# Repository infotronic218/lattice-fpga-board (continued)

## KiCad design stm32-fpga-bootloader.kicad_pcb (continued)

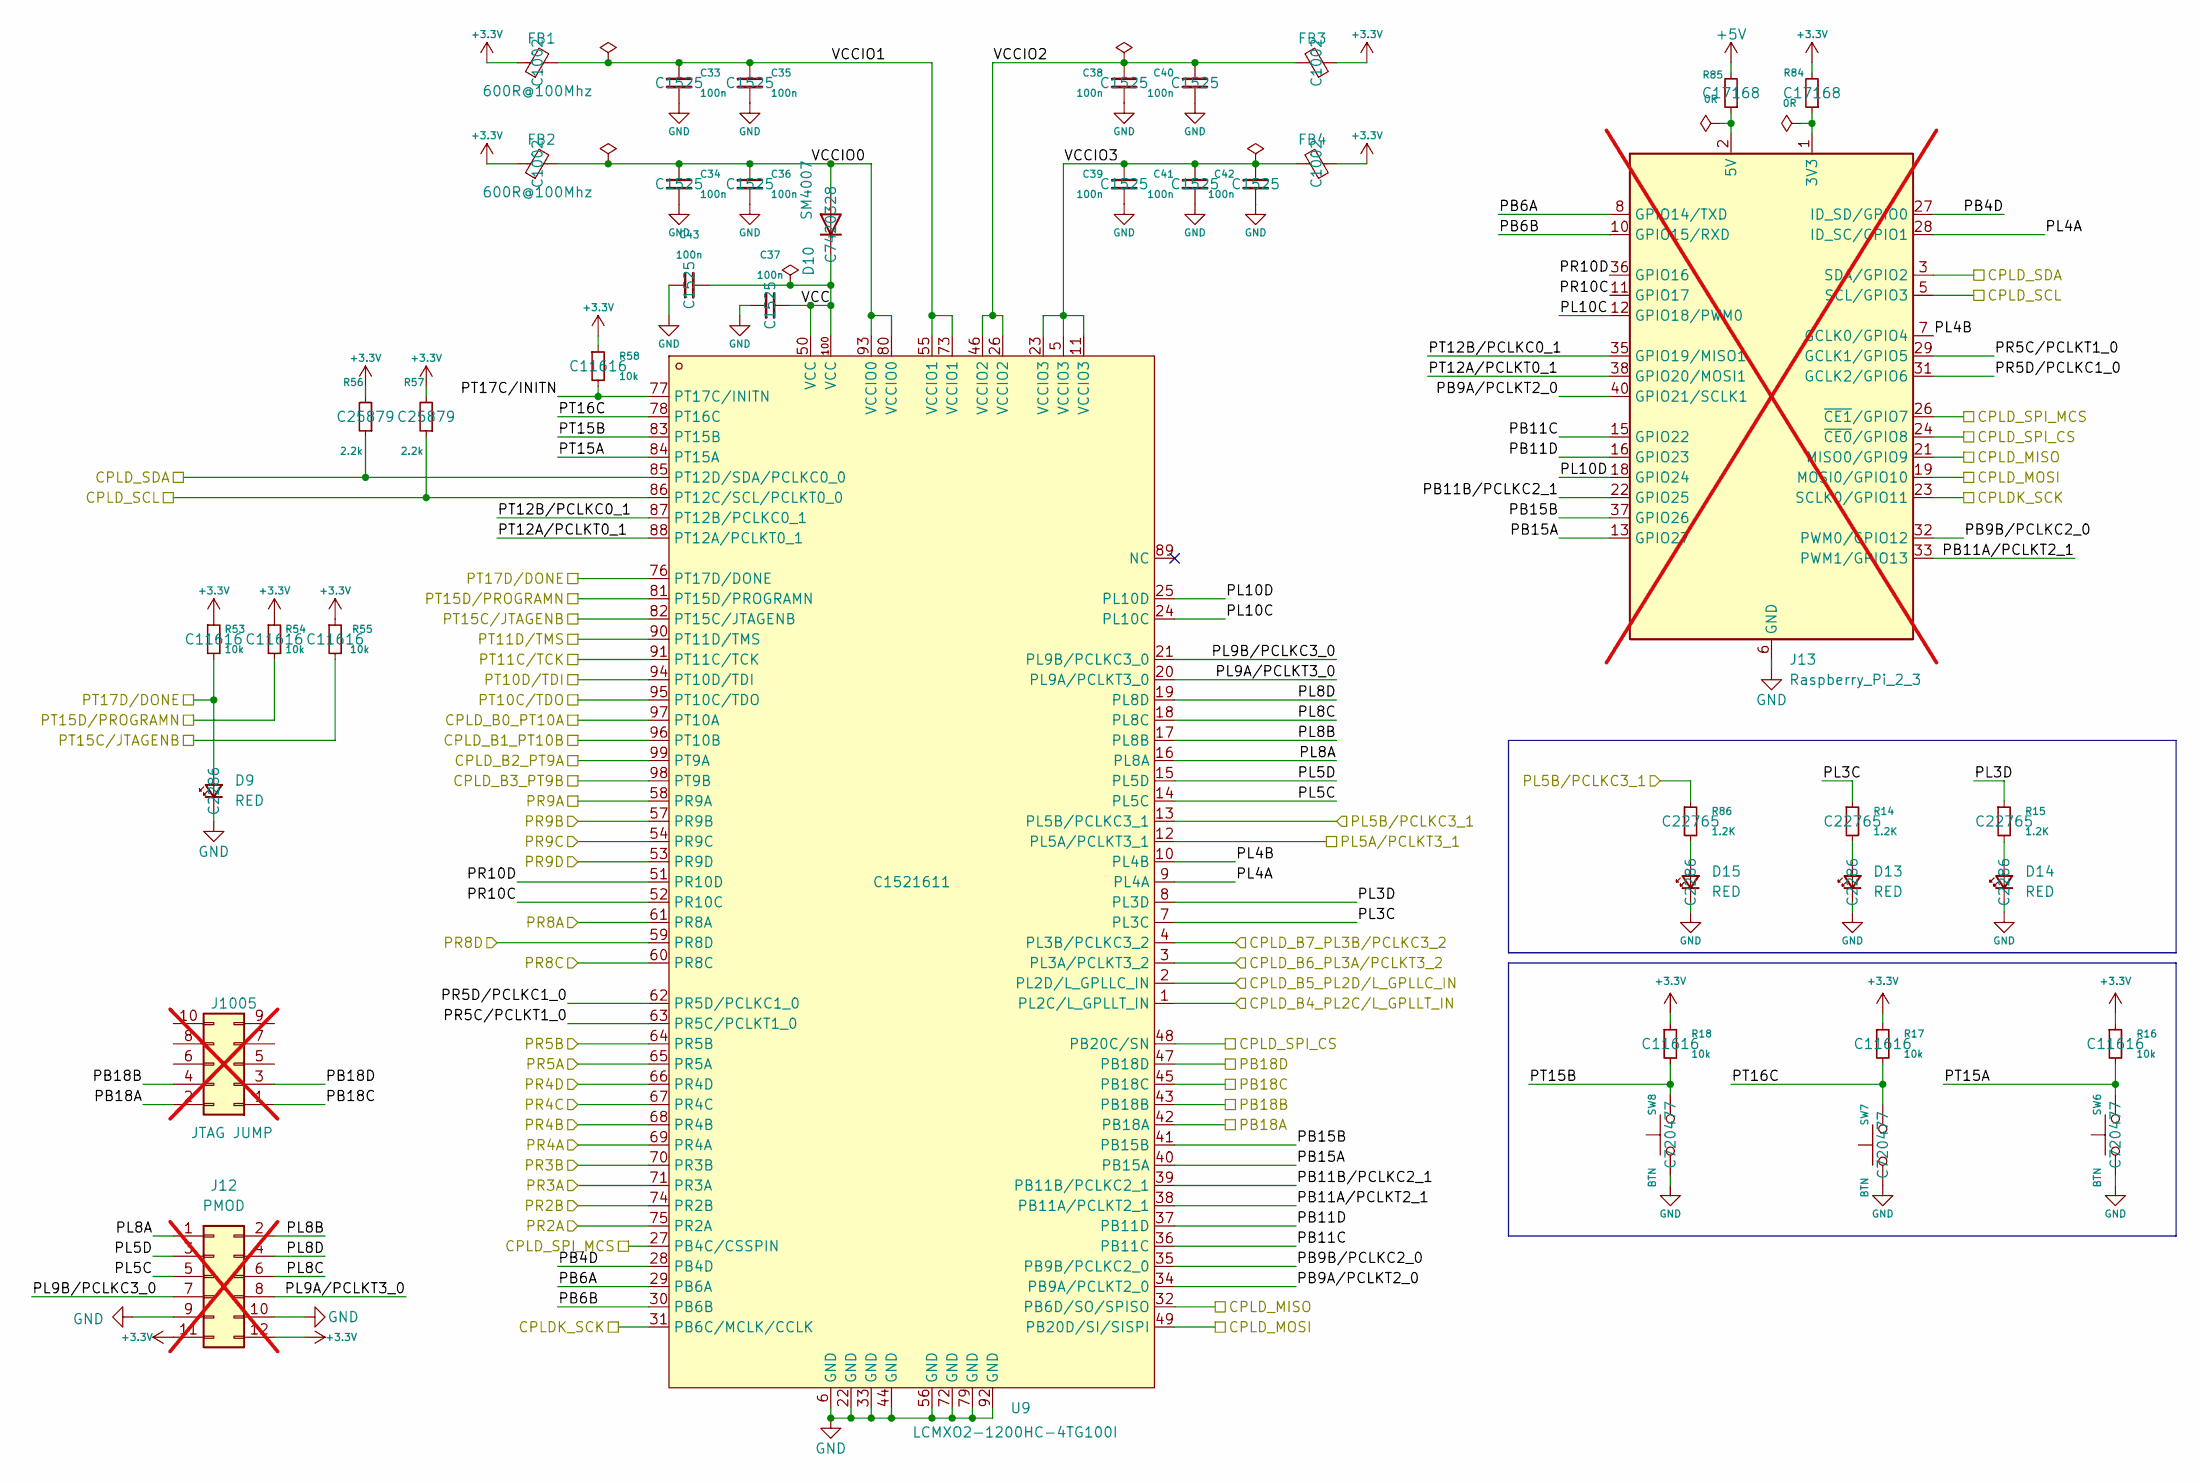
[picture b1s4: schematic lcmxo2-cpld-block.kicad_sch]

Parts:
C33, C34, C35, C36, C37, C38, C39, C40, C41, C42, C43: 100n; C_0402_1005Metric; LCSC C1525
D9, D13, D14, D15: RED; LED_0603_1608Metric; LCSC C2286
D10: SM4007; D_SOD-123F; LCSC C7420328
FB1, FB2, FB3, FB4: 600R@100Mhz; L_0603_1608Metric; LCSC C1002
J12: PMOD; PinSocket_2x06_P2.54mm_Horizontal; not fitted
J13: Raspberry_Pi_2_3; PinHeader_2x20_P2.54mm_Vertical; not fitted
J1005: JTAG JUMP; PinSocket_2x05_P2.54mm_Vertical; not fitted
R14, R15, R86: 1.2K; R_0603_1608Metric; LCSC C22765
R16, R17, R18, R53, R54, R55, R58: 10k; R_0402_1005Metric; LCSC C11616
R56, R57: 2.2k; R_0402_1005Metric; LCSC C25879
R84, R85: 0R; R_0402_1005Metric; LCSC C17168
SW6, SW7, SW8: BTN; SW-SMD_L3.9-W3.0-P4.45; LCSC C720477
U9: LCMXO2-1200HC-4TG100I; TQFP-100_14x14mm_P0.5mm; LCSC Part Name LCMXO2 1200HC 4TG100I

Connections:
+3.3V: FB1.1, FB2.1, FB3.1, FB4.1, J12.11, J12.12, R16.1, R17.1, R18.1, R53.1, R54.1, R55.1, R56.2, R57.2, R58.1, R84.2; also elsewhere on the board
+5V: R85.2; also elsewhere on the board
/CPLDK_SCK: J13.23 (SCLK0/GPIO11), U9.31 (PB6C/MCLK/CCLK); also elsewhere on the board
/CPLD_B0_PT10A: U9.97 (PT10A); also elsewhere on the board
/CPLD_B1_PT10B: U9.96 (PT10B); also elsewhere on the board
/CPLD_B2_PT9A: U9.99 (PT9A); also elsewhere on the board
/CPLD_B3_PT9B: U9.98 (PT9B); also elsewhere on the board
/CPLD_B4_PL2C/L_GPLLT_IN: U9.1 (PL2C/L_GPLLT_IN); also elsewhere on the board
/CPLD_B5_PL2D/L_GPLLC_IN: U9.2 (PL2D/L_GPLLC_IN); also elsewhere on the board
/CPLD_B6_PL3A/PCLKT3_2: U9.3 (PL3A/PCLKT3_2); also elsewhere on the board
/CPLD_B7_PL3B/PCLKC3_2: U9.4 (PL3B/PCLKC3_2); also elsewhere on the board
/CPLD_CLOCK: U9.12 (PL5A/PCLKT3_1); also elsewhere on the board
/CPLD_MISO: J13.21 (MISO0/GPIO9), U9.32 (PB6D/SO/SPISO); also elsewhere on the board
/CPLD_MOSI: J13.19 (MOSI0/GPIO10), U9.49 (PB20D/SI/SISPI); also elsewhere on the board
/CPLD_SCL: J13.5 (SCL/GPIO3), R57.1, U9.86 (PT12C/SCL/PCLKT0_0); also elsewhere on the board
/CPLD_SDA: J13.3 (SDA/GPIO2), R56.1, U9.85 (PT12D/SDA/PCLKC0_0); also elsewhere on the board
/CPLD_SPI_CS: J13.24 (~CE0/GPIO8), U9.48 (PB20C/SN); also elsewhere on the board
/CPLD_SPI_MCS: J13.26 (~CE1/GPIO7), U9.27 (PB4C/CSSPIN); also elsewhere on the board
/PB18A: J1005.2, U9.42 (PB18A)
/PB18B: J1005.4, U9.43 (PB18B)
/PB18C: J1005.1, U9.45 (PB18C)
/PB18D: J1005.3, U9.47 (PB18D)
/PR2A: U9.75 (PR2A); also elsewhere on the board
/PR2B: U9.74 (PR2B); also elsewhere on the board
/PR3A: U9.71 (PR3A); also elsewhere on the board
/PR3B: U9.70 (PR3B); also elsewhere on the board
/PR4A: U9.69 (PR4A); also elsewhere on the board
/PR4B: U9.68 (PR4B); also elsewhere on the board
/PR4C: U9.67 (PR4C); also elsewhere on the board
/PR4D: U9.66 (PR4D); also elsewhere on the board
/PR5A: U9.65 (PR5A); also elsewhere on the board
/PR5B: U9.64 (PR5B); also elsewhere on the board
/PR8A: U9.61 (PR8A); also elsewhere on the board
/PR8C: U9.60 (PR8C); also elsewhere on the board
/PR8D: U9.59 (PR8D); also elsewhere on the board
/PR9A: U9.58 (PR9A); also elsewhere on the board
/PR9B: U9.57 (PR9B); also elsewhere on the board
/PR9C: U9.54 (PR9C); also elsewhere on the board
/PR9D: U9.53 (PR9D); also elsewhere on the board
/PT10C/TDO: U9.95 (PT10C/TDO); also elsewhere on the board
/PT10D/TDI: U9.94 (PT10D/TDI); also elsewhere on the board
/PT11C/TCK: U9.91 (PT11C/TCK); also elsewhere on the board
/PT11D/TMS: U9.90 (PT11D/TMS); also elsewhere on the board
/jtag-prog/CLK: R86.1, U9.13 (PL5B/PCLKC3_1); also elsewhere on the board
/lcmxo2-cpld-block/PB4D: J13.27 (ID_SD/GPIO0), U9.28 (PB4D)
/lcmxo2-cpld-block/PB6A: J13.8 (GPIO14/TXD), U9.29 (PB6A)
/lcmxo2-cpld-block/PB6B: J13.10 (GPIO15/RXD), U9.30 (PB6B)
/lcmxo2-cpld-block/PB9A/PCLKT2_0: J13.40 (GPIO21/SCLK1), U9.34 (PB9A/PCLKT2_0)
/lcmxo2-cpld-block/PB9B/PCLKC2_0: J13.32 (PWM0/GPIO12), U9.35 (PB9B/PCLKC2_0)
/lcmxo2-cpld-block/PB11A/PCLKT2_1: J13.33 (PWM1/GPIO13), U9.38 (PB11A/PCLKT2_1)
/lcmxo2-cpld-block/PB11B/PCLKC2_1: J13.22 (GPIO25), U9.39 (PB11B/PCLKC2_1)
/lcmxo2-cpld-block/PB11C: J13.15 (GPIO22), U9.36 (PB11C)
/lcmxo2-cpld-block/PB11D: J13.16 (GPIO23), U9.37 (PB11D)
/lcmxo2-cpld-block/PB15A: J13.13 (GPIO27), U9.40 (PB15A)
/lcmxo2-cpld-block/PB15B: J13.37 (GPIO26), U9.41 (PB15B)
/lcmxo2-cpld-block/PL3C: R14.1, U9.7 (PL3C)
/lcmxo2-cpld-block/PL3D: R15.1, U9.8 (PL3D)
/lcmxo2-cpld-block/PL4A: J13.28 (ID_SC/GPIO1), U9.9 (PL4A)
/lcmxo2-cpld-block/PL4B: J13.7 (GCLK0/GPIO4), U9.10 (PL4B)
/lcmxo2-cpld-block/PL5C: J12.5, U9.14 (PL5C)
/lcmxo2-cpld-block/PL5D: J12.3, U9.15 (PL5D)
/lcmxo2-cpld-block/PL8A: J12.1, U9.16 (PL8A)
/lcmxo2-cpld-block/PL8B: J12.2, U9.17 (PL8B)
/lcmxo2-cpld-block/PL8C: J12.6, U9.18 (PL8C)
/lcmxo2-cpld-block/PL8D: J12.4, U9.19 (PL8D)
/lcmxo2-cpld-block/PL9A/PCLKT3_0: J12.8, U9.20 (PL9A/PCLKT3_0)
/lcmxo2-cpld-block/PL9B/PCLKC3_0: J12.7, U9.21 (PL9B/PCLKC3_0)
/lcmxo2-cpld-block/PL10C: J13.12 (GPIO18/PWM0), U9.24 (PL10C)
/lcmxo2-cpld-block/PL10D: J13.18 (GPIO24), U9.25 (PL10D)
/lcmxo2-cpld-block/PR5C/PCLKT1_0: J13.29 (GCLK1/GPIO5), U9.63 (PR5C/PCLKT1_0)
/lcmxo2-cpld-block/PR5D/PCLKC1_0: J13.31 (GCLK2/GPIO6), U9.62 (PR5D/PCLKC1_0)
/lcmxo2-cpld-block/PR10C: J13.11 (GPIO17), U9.52 (PR10C)
/lcmxo2-cpld-block/PR10D: J13.36 (GPIO16), U9.51 (PR10D)
/lcmxo2-cpld-block/PT12A/PCLKT0_1: J13.38 (GPIO20/MOSI1), U9.88 (PT12A/PCLKT0_1)
/lcmxo2-cpld-block/PT12B/PCLKC0_1: J13.35 (GPIO19/MISO1), U9.87 (PT12B/PCLKC0_1)
/lcmxo2-cpld-block/PT15A: R16.2, SW6.2, U9.84 (PT15A)
/lcmxo2-cpld-block/PT15B: R18.2, SW8.2, U9.83 (PT15B)
/lcmxo2-cpld-block/PT15C/JTAGENB: R55.2, U9.82 (PT15C/JTAGENB)
/lcmxo2-cpld-block/PT15D/PROGRAMN: R54.2, U9.81 (PT15D/PROGRAMN)
/lcmxo2-cpld-block/PT16C: R17.2, SW7.2, U9.78 (PT16C)
/lcmxo2-cpld-block/PT17C/INITN: R58.2, U9.77 (PT17C/INITN)
/lcmxo2-cpld-block/PT17D/DONE: D9.2 (A), R53.2, U9.76 (PT17D/DONE)
/lcmxo2-cpld-block/VCC: C37.2, C43.2, D10.1 (K), U9.50 (VCC), U9.100 (VCC)
/lcmxo2-cpld-block/VCCIO0: C34.1, C36.1, D10.2 (A), FB2.2, U9.80 (VCCIO0), U9.93 (VCCIO0)
/lcmxo2-cpld-block/VCCIO1: C33.1, C35.1, FB1.2, U9.55 (VCCIO1), U9.73 (VCCIO1)
/lcmxo2-cpld-block/VCCIO2: C38.1, C40.1, FB3.2, U9.26 (VCCIO2), U9.46 (VCCIO2)
/lcmxo2-cpld-block/VCCIO3: C39.1, C41.1, C42.1, FB4.2, U9.5 (VCCIO3), U9.11 (VCCIO3), U9.23 (VCCIO3)
GND: C33.2, C34.2, C35.2, C36.2, C37.1, C38.2, C39.2, C40.2, C41.2, C42.2, C43.1, D9.1 (K), D13.1 (K), D14.1 (K), D15.1 (K), J12.9, J12.10, J13.6 (GND), J13.9 (GND), J13.14 (GND), J13.20 (GND), J13.25 (GND), J13.30 (GND), J13.34 (GND), J13.39 (GND), SW6.1, SW7.1, SW8.1, U9.6 (GND), U9.22 (GND), U9.33 (GND), U9.44 (GND), U9.56 (GND), U9.72 (GND), U9.79 (GND), U9.92 (GND); also elsewhere on the board
unnamed: D13.2 (A), R14.2
unnamed: D14.2 (A), R15.2
unnamed: D15.2 (A), R86.2
unnamed: J13.1 (3V3), J13.17 (3V3), R84.1
unnamed: J13.2 (5V), J13.4 (5V), R85.1

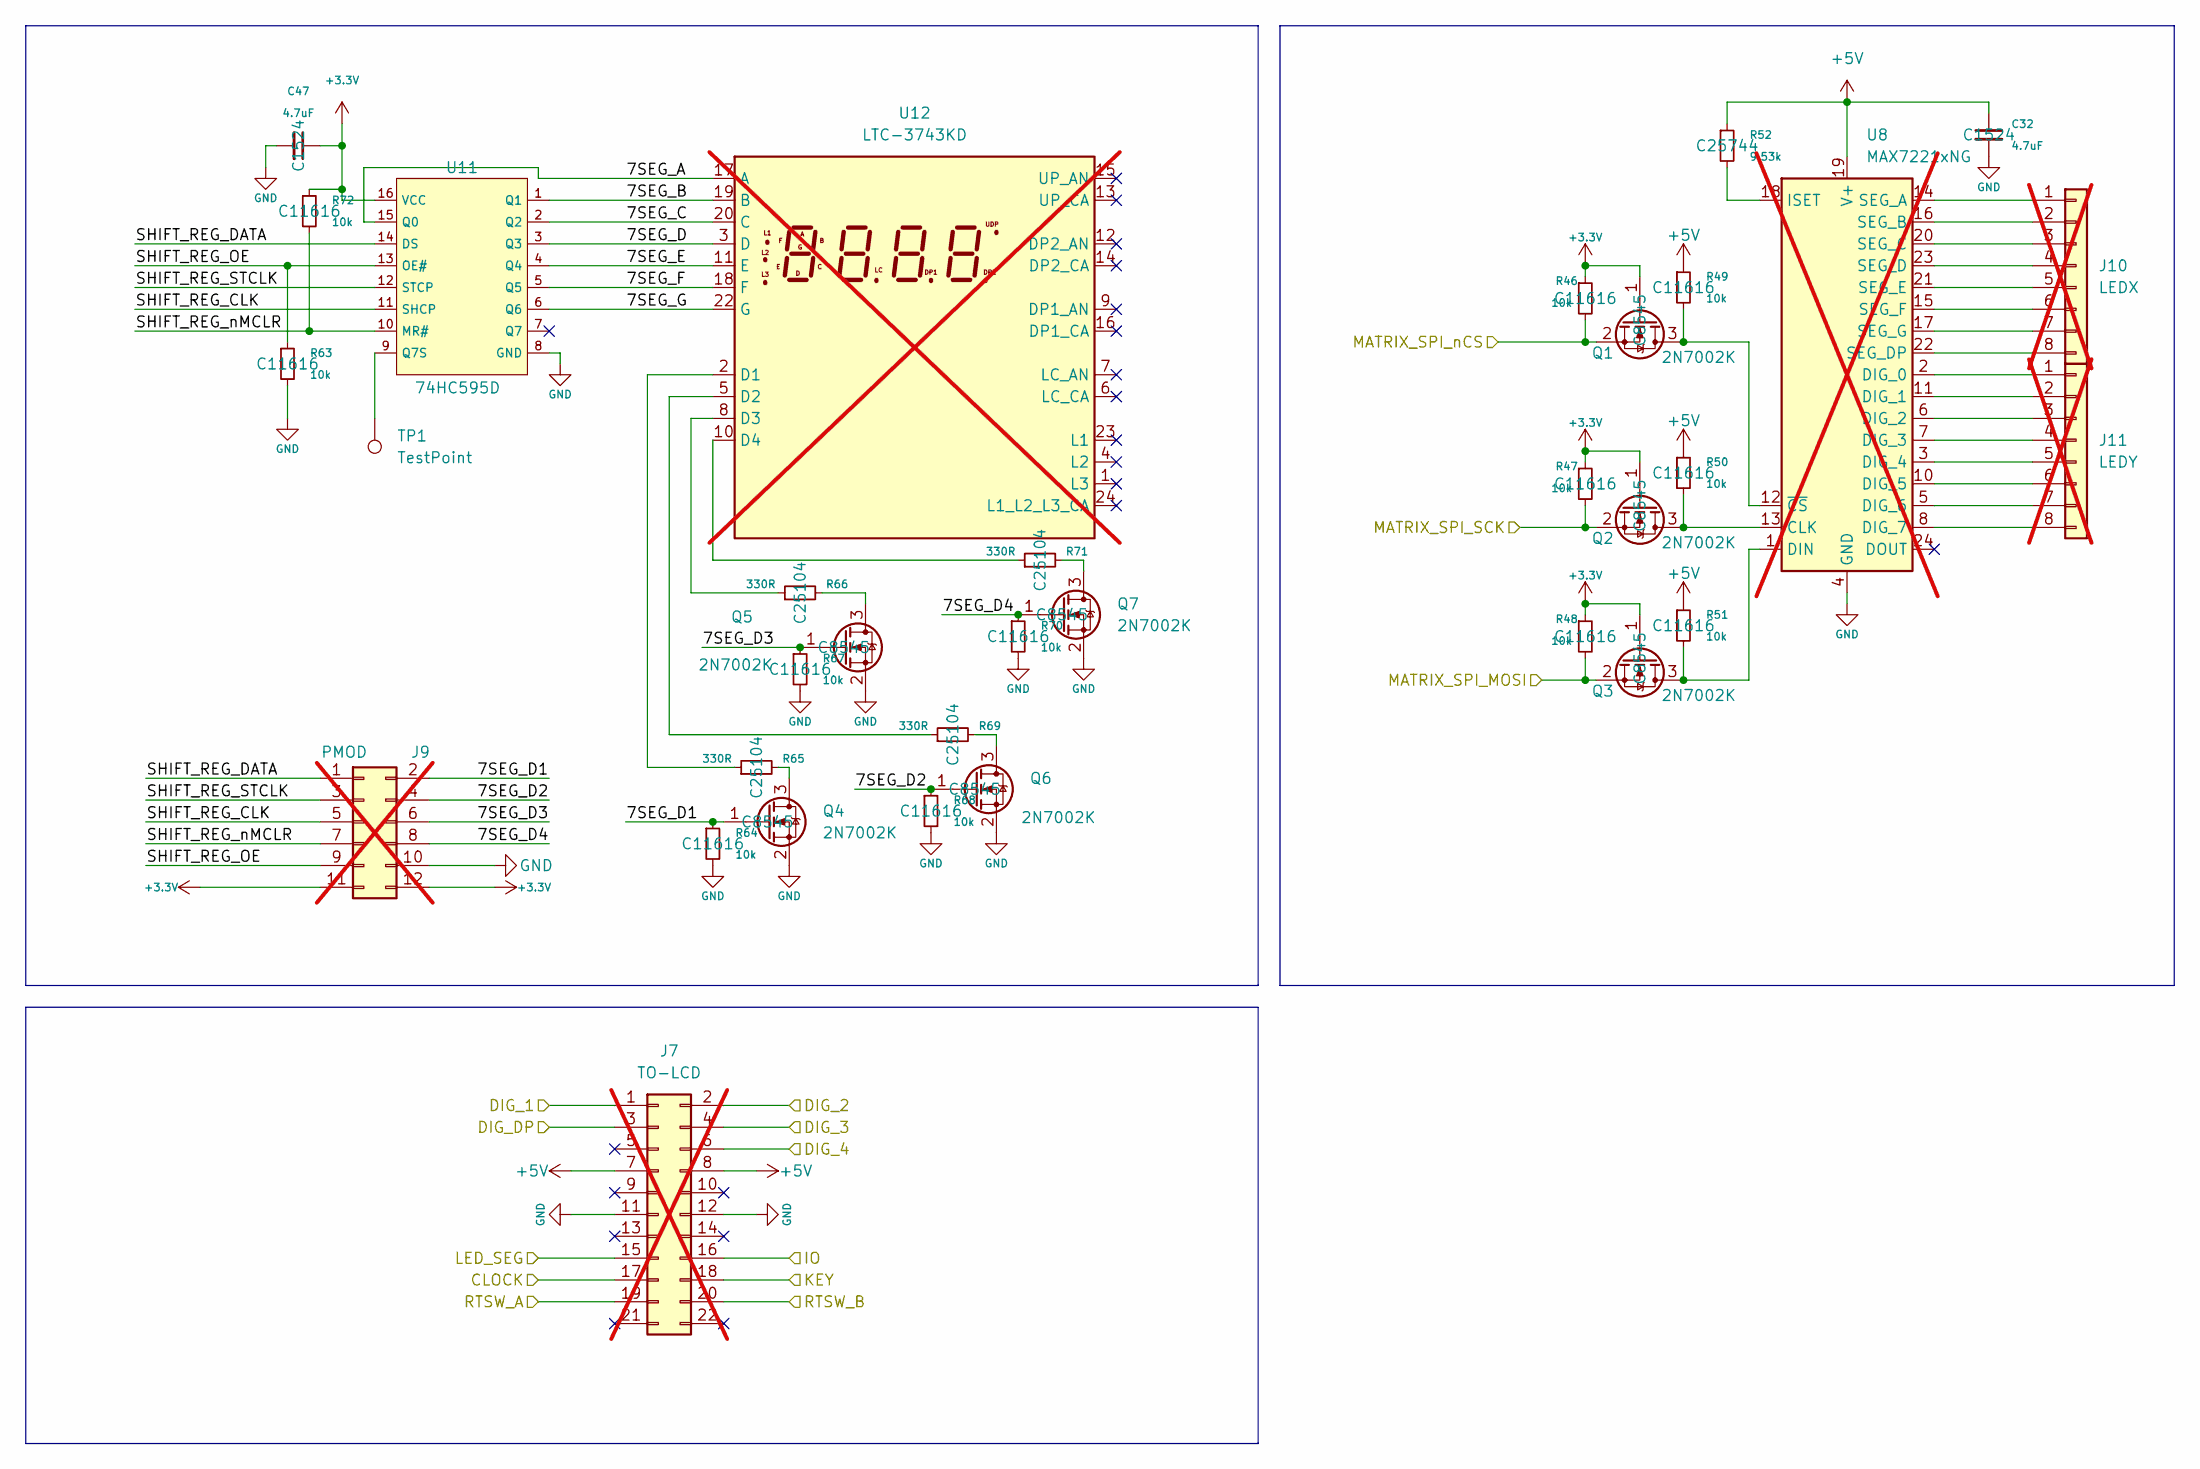
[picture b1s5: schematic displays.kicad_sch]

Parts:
C32, C47: 4.7uF; C_0603_1608Metric; LCSC C1524
J7: TO-LCD; CON_536470274_MOL; not fitted
J9: PMOD; PinSocket_2x06_P2.54mm_Vertical; not fitted
J10: LEDX; PinSocket_1x08_P2.54mm_Vertical; not fitted
J11: LEDY; PinSocket_1x08_P2.54mm_Vertical; not fitted
Q1, Q2, Q3, Q4, Q5, Q6, Q7: 2N7002K; SOT-23; LCSC C8545
R46, R47, R48, R49, R50, R51, R63, R64, R67, R68, R70, R72: 10k; R_0402_1005Metric; LCSC C11616
R52: 9.53k; R_0402_1005Metric; LCSC C25744
R65, R66, R69, R71: 330R; R_0402_1005Metric; LCSC C25104
TP1: TestPoint; TestPoint_Pad_1.0x1.0mm
U8: MAX7221xNG; DIP-24_W7.62mm; not fitted
U11: 74HC595D; SOIC-16_L9.9-W3.9-P1.27-LS6.0-BL; LCSC C5947
U12: LTC-3743KD; not fitted

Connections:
+3.3V: C47.1, J9.11, J9.12, Q1.1 (G), Q2.1 (G), Q3.1 (G), R46.1, R47.1, R48.1, R72.1, U11.16 (VCC); also elsewhere on the board
+5V: C32.1, J7.7, J7.8, R49.1, R50.1, R51.1, R52.1, U8.19 (V+); also elsewhere on the board
/MATRIX_SPI_MOSI: Q3.2 (S), R48.2; also elsewhere on the board
/MATRIX_SPI_SCK: Q2.2 (S), R47.2; also elsewhere on the board
/MATRIX_SPI_nCS: Q1.2 (S), R46.2; also elsewhere on the board
/PR4C: J7.1; also elsewhere on the board
/PR4D: J7.3; also elsewhere on the board
/PR5A: J7.2; also elsewhere on the board
/PR5B: J7.4; also elsewhere on the board
/PR8A: J7.6; also elsewhere on the board
/PR8C: J7.16; also elsewhere on the board
/PR8D: J7.18; also elsewhere on the board
/PR9A: J7.20; also elsewhere on the board
/PR9B: J7.17; also elsewhere on the board
/PR9C: J7.19; also elsewhere on the board
/PR9D: J7.15; also elsewhere on the board
/displays/7SEG_A: U11.15 (Q0), U12.17 (A)
/displays/7SEG_B: U11.1 (Q1), U12.19 (B)
/displays/7SEG_C: U11.2 (Q2), U12.20 (C)
/displays/7SEG_D: U11.3 (Q3), U12.3 (D)
/displays/7SEG_D1: J9.2, Q4.1 (G), R64.1
/displays/7SEG_D2: J9.4, Q6.1 (G), R68.1
/displays/7SEG_D3: J9.6, Q5.1 (G), R67.1
/displays/7SEG_D4: J9.8, Q7.1 (G), R70.1
/displays/7SEG_E: U11.4 (Q4), U12.11 (E), U12.21 (D1_E_AN)
/displays/7SEG_F: U11.5 (Q5), U12.18 (F)
/displays/7SEG_G: U11.6 (Q6), U12.22 (G)
/displays/SHIFT_REG_CLK: J9.5, U11.11 (SHCP)
/displays/SHIFT_REG_DATA: J9.1, U11.14 (DS)
/displays/SHIFT_REG_OE: J9.9, R63.1, U11.13 (OE#)
/displays/SHIFT_REG_STCLK: J9.3, U11.12 (STCP)
/displays/SHIFT_REG_nMCLR: J9.7, R72.2, U11.10 (MR#)
GND: C32.2, C47.2, J7.11, J7.12, J9.10, Q4.2 (S), Q5.2 (S), Q6.2 (S), Q7.2 (S), R63.2, R64.2, R67.2, R68.2, R70.2, U8.4 (GND), U8.9 (GND), U11.8 (GND); also elsewhere on the board
unnamed: J10.1, U8.14 (SEG_A)
unnamed: J10.2, U8.16 (SEG_B)
unnamed: J10.3, U8.20 (SEG_C)
unnamed: J10.4, U8.23 (SEG_D)
unnamed: J10.5, U8.21 (SEG_E)
unnamed: J10.6, U8.15 (SEG_F)
unnamed: J10.7, U8.17 (SEG_G)
unnamed: J10.8, U8.22 (SEG_DP)
unnamed: J11.1, U8.2 (DIG_0)
unnamed: J11.2, U8.11 (DIG_1)
unnamed: J11.3, U8.6 (DIG_2)
unnamed: J11.4, U8.7 (DIG_3)
unnamed: J11.5, U8.3 (DIG_4)
unnamed: J11.6, U8.10 (DIG_5)
unnamed: J11.7, U8.5 (DIG_6)
unnamed: J11.8, U8.8 (DIG_7)
unnamed: Q1.3 (D), R49.2, U8.12 (~CS)
unnamed: Q2.3 (D), R50.2, U8.13 (CLK)
unnamed: Q3.3 (D), R51.2, U8.1 (DIN)
unnamed: Q4.3 (D), R65.2
unnamed: Q5.3 (D), R66.2
unnamed: Q6.3 (D), R69.2
unnamed: Q7.3 (D), R71.2
unnamed: R52.2, U8.18 (ISET)
unnamed: TP1.1, U11.9 (Q7S)
unnamed: R65.1, U12.2 (D1)
unnamed: R69.1, U12.5 (D2)
unnamed: R66.1, U12.8 (D3)
unnamed: R71.1, U12.10 (D4)

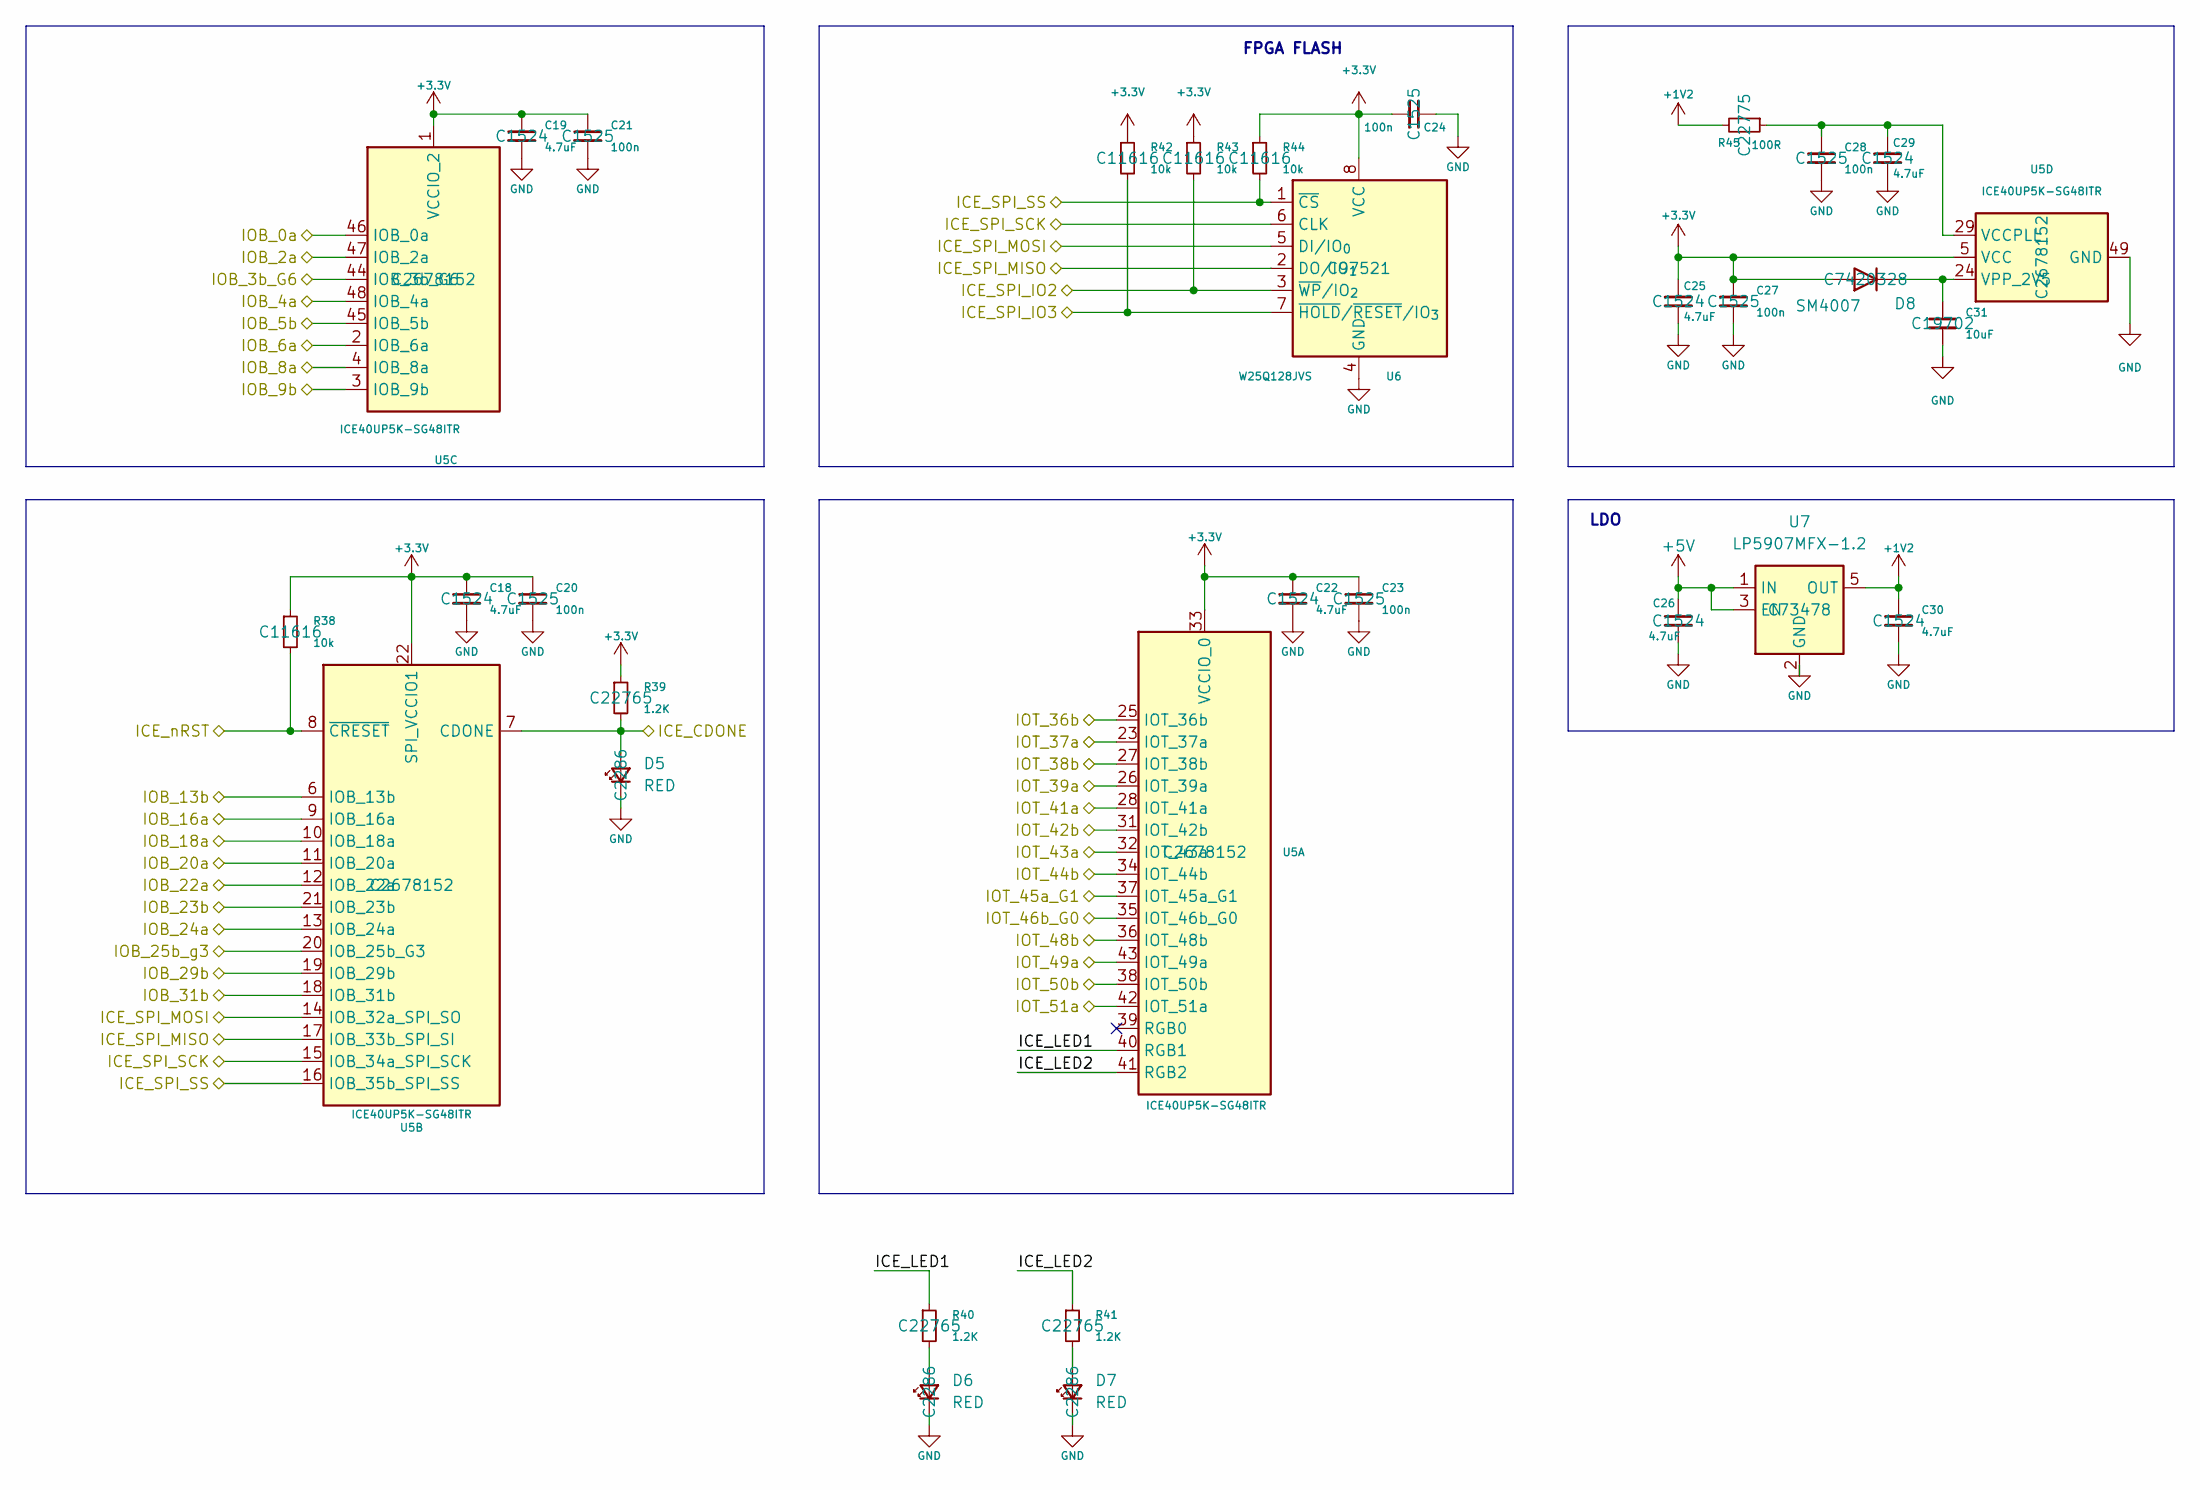
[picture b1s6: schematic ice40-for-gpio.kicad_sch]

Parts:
C18, C19, C22, C25, C26, C29, C30: 4.7uF; C_0603_1608Metric; LCSC C1524
C20, C21, C23, C24, C27, C28: 100n; C_0402_1005Metric; LCSC C1525
C31: 10uF; C_0603_1608Metric; LCSC C19702
D5, D6, D7: RED; LED_0603_1608Metric; LCSC C2286
D8: SM4007; D_SOD-123F; LCSC C7420328
R38, R42, R43, R44: 10k; R_0402_1005Metric; LCSC C11616
R39, R40, R41: 1.2K; R_0603_1608Metric; LCSC C22765
R45: 100R; R_0603_1608Metric; LCSC C22775
U5: ICE40UP5K-SG48ITR; QFN-48-1EP_7x7mm_P0.5mm_EP5.6x5.6mm; LCSC C2678152
U6: W25Q128JVS; SOIC-8_5.3x5.3mm_P1.27mm; LCSC C97521
U7: LP5907MFX-1.2; SOT-23-5; LCSC C73478

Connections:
+1V2: C30.1, R45.2, U7.5 (OUT)
+3.3V: C18.1, C19.1, C20.1, C21.1, C22.1, C23.1, C24.2, C25.1, C27.1, D8.2 (A), R38.1, R39.1, R42.1, R43.1, R44.1, U5.1 (VCCIO_2), U5.5 (VCC), U5.22 (SPI_VCCIO1), U5.30 (VCC), U5.33 (VCCIO_0), U6.8 (VCC); also elsewhere on the board
+5V: C26.1, U7.1 (IN), U7.3 (EN); also elsewhere on the board
/ICE_CDONE: D5.2 (A), R39.2, U5.7 (CDONE); also elsewhere on the board
/ICE_CLOCK: U5.35 (IOT_46b_G0); also elsewhere on the board
/ICE_SPI_MISO: U5.17 (IOB_33b_SPI_SI), U6.2 (DO/IO_{1}); also elsewhere on the board
/ICE_SPI_MOSI: U5.14 (IOB_32a_SPI_SO), U6.5 (DI/IO_{0}); also elsewhere on the board
/ICE_SPI_SCK: U5.15 (IOB_34a_SPI_SCK), U6.6 (CLK); also elsewhere on the board
/ICE_SPI_SS: R44.2, U5.16 (IOB_35b_SPI_SS), U6.1 (~CS); also elsewhere on the board
/ICE_USB_N: U5.9 (IOB_16a); also elsewhere on the board
/ICE_USB_P: U5.10 (IOB_18a); also elsewhere on the board
/ICE_nRST: R38.2, U5.8 (~CRESET); also elsewhere on the board
/IOB_0a: U5.46 (IOB_0a); also elsewhere on the board
/IOB_2a: U5.47 (IOB_2a); also elsewhere on the board
/IOB_3b_G6: U5.44 (IOB_3b_G6); also elsewhere on the board
/IOB_4a: U5.48 (IOB_4a); also elsewhere on the board
/IOB_5b: U5.45 (IOB_5b); also elsewhere on the board
/IOB_6a: U5.2 (IOB_6a); also elsewhere on the board
/IOB_8a: U5.4 (IOB_8a); also elsewhere on the board
/IOB_13b: U5.6 (IOB_13b); also elsewhere on the board
/IOB_20a: U5.11 (IOB_20a); also elsewhere on the board
/IOB_22a: U5.12 (IOB_22a); also elsewhere on the board
/IOB_23b: U5.21 (IOB_23b); also elsewhere on the board
/IOT_36b: U5.25 (IOT_36b); also elsewhere on the board
/IOT_37a: U5.23 (IOT_37a); also elsewhere on the board
/IOT_38b: U5.27 (IOT_38b); also elsewhere on the board
/IOT_39a: U5.26 (IOT_39a); also elsewhere on the board
/IOT_43a: U5.32 (IOT_43a); also elsewhere on the board
/IOT_44b: U5.34 (IOT_44b); also elsewhere on the board
/IOT_45a_G1: U5.37 (IOT_45a_G1); also elsewhere on the board
/IOT_48b: U5.36 (IOT_48b); also elsewhere on the board
/IOT_50b: U5.38 (IOT_50b); also elsewhere on the board
/IOT_51a: U5.42 (IOT_51a); also elsewhere on the board
/RPI_ICE0: U5.3 (IOB_9b); also elsewhere on the board
/RPI_ICE1: U5.31 (IOT_42b); also elsewhere on the board
/RPI_ICE2: U5.19 (IOB_29b); also elsewhere on the board
/RPI_ICE3: U5.13 (IOB_24a); also elsewhere on the board
/RPI_ICE4: U5.20 (IOB_25b_G3); also elsewhere on the board
/RPI_ICE5: U5.18 (IOB_31b); also elsewhere on the board
/RPI_ICE6: U5.43 (IOT_49a); also elsewhere on the board
/RPI_ICE7: U5.28 (IOT_41a); also elsewhere on the board
/ice40-for-gpio/ICE_LED1: R40.1, U5.40 (RGB1)
/ice40-for-gpio/ICE_LED2: R41.1, U5.41 (RGB2)
/ice40-for-gpio/ICE_SPI_IO2: R43.2, U6.3 (~WP/IO_{2})
/ice40-for-gpio/ICE_SPI_IO3: R42.2, U6.7 (~HOLD/~RESET/IO_{3})
GND: C18.2, C19.2, C20.2, C21.2, C22.2, C23.2, C24.1, C25.2, C26.2, C27.2, C28.2, C29.2, C30.2, C31.2, D5.1 (K), D6.1 (K), D7.1 (K), U5.49 (GND), U6.4 (GND), U7.2 (GND); also elsewhere on the board
unnamed: D6.2 (A), R40.2
unnamed: D7.2 (A), R41.2
unnamed: C31.1, D8.1 (K), U5.24 (VPP_2V5)
unnamed: C28.1, C29.1, R45.1, U5.29 (VCCPLL)

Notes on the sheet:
LDO
FPGA FLASH

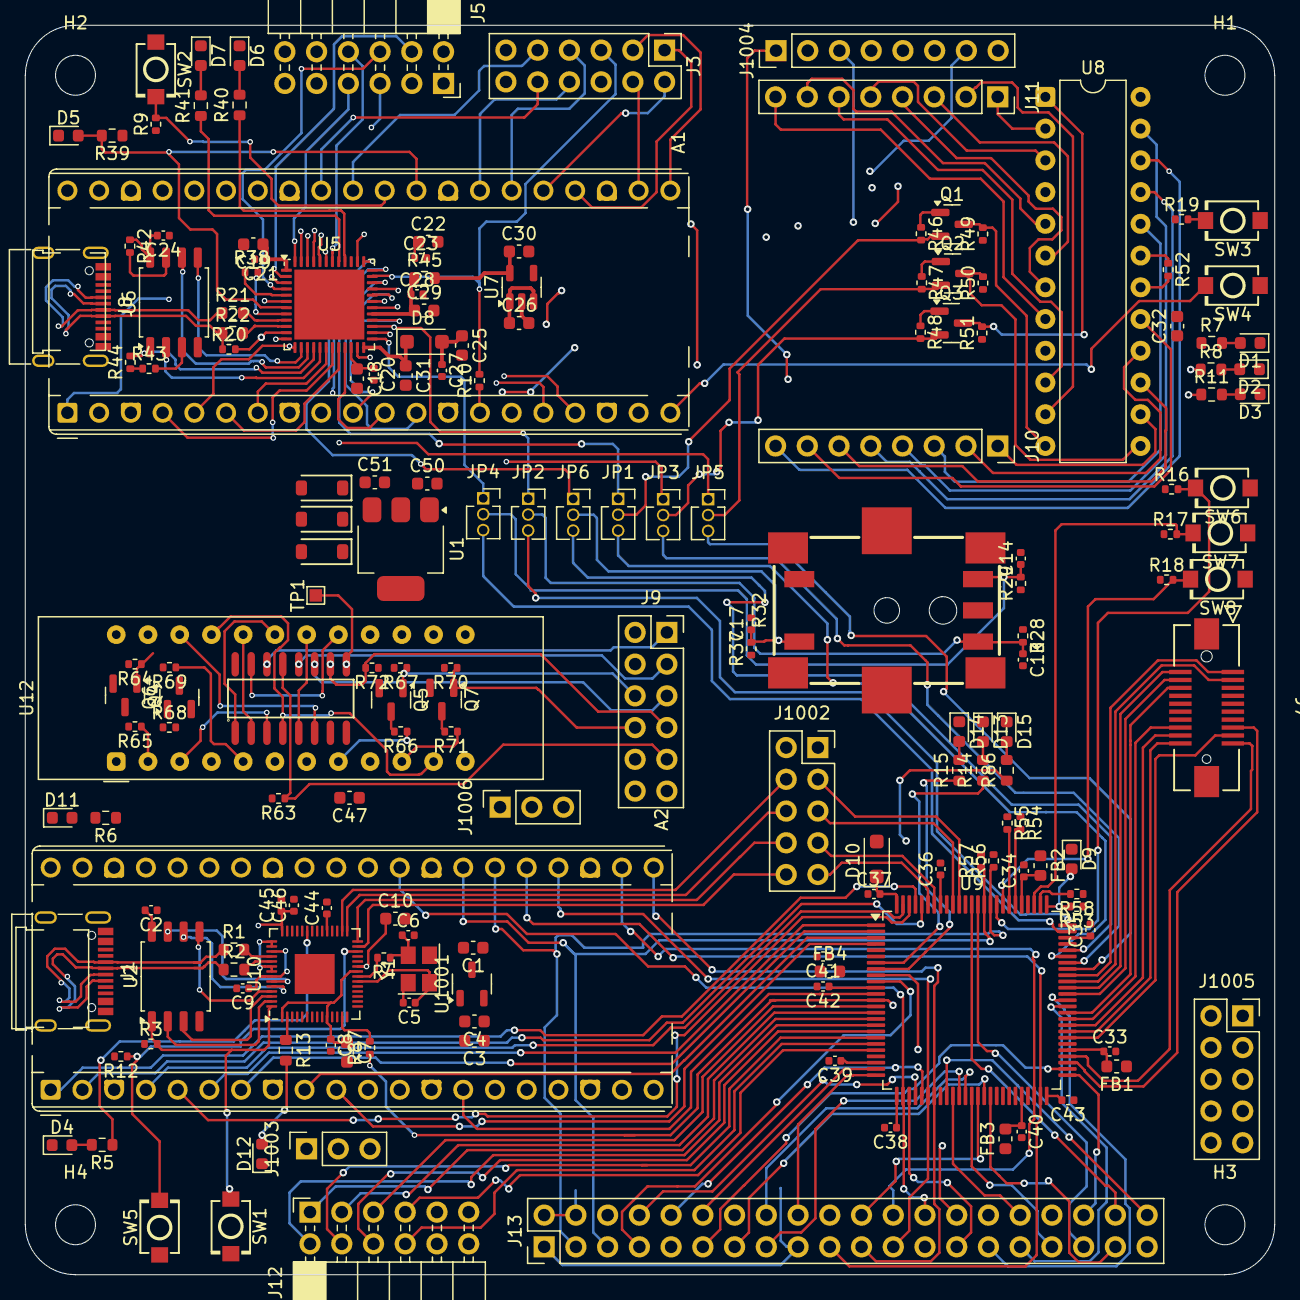
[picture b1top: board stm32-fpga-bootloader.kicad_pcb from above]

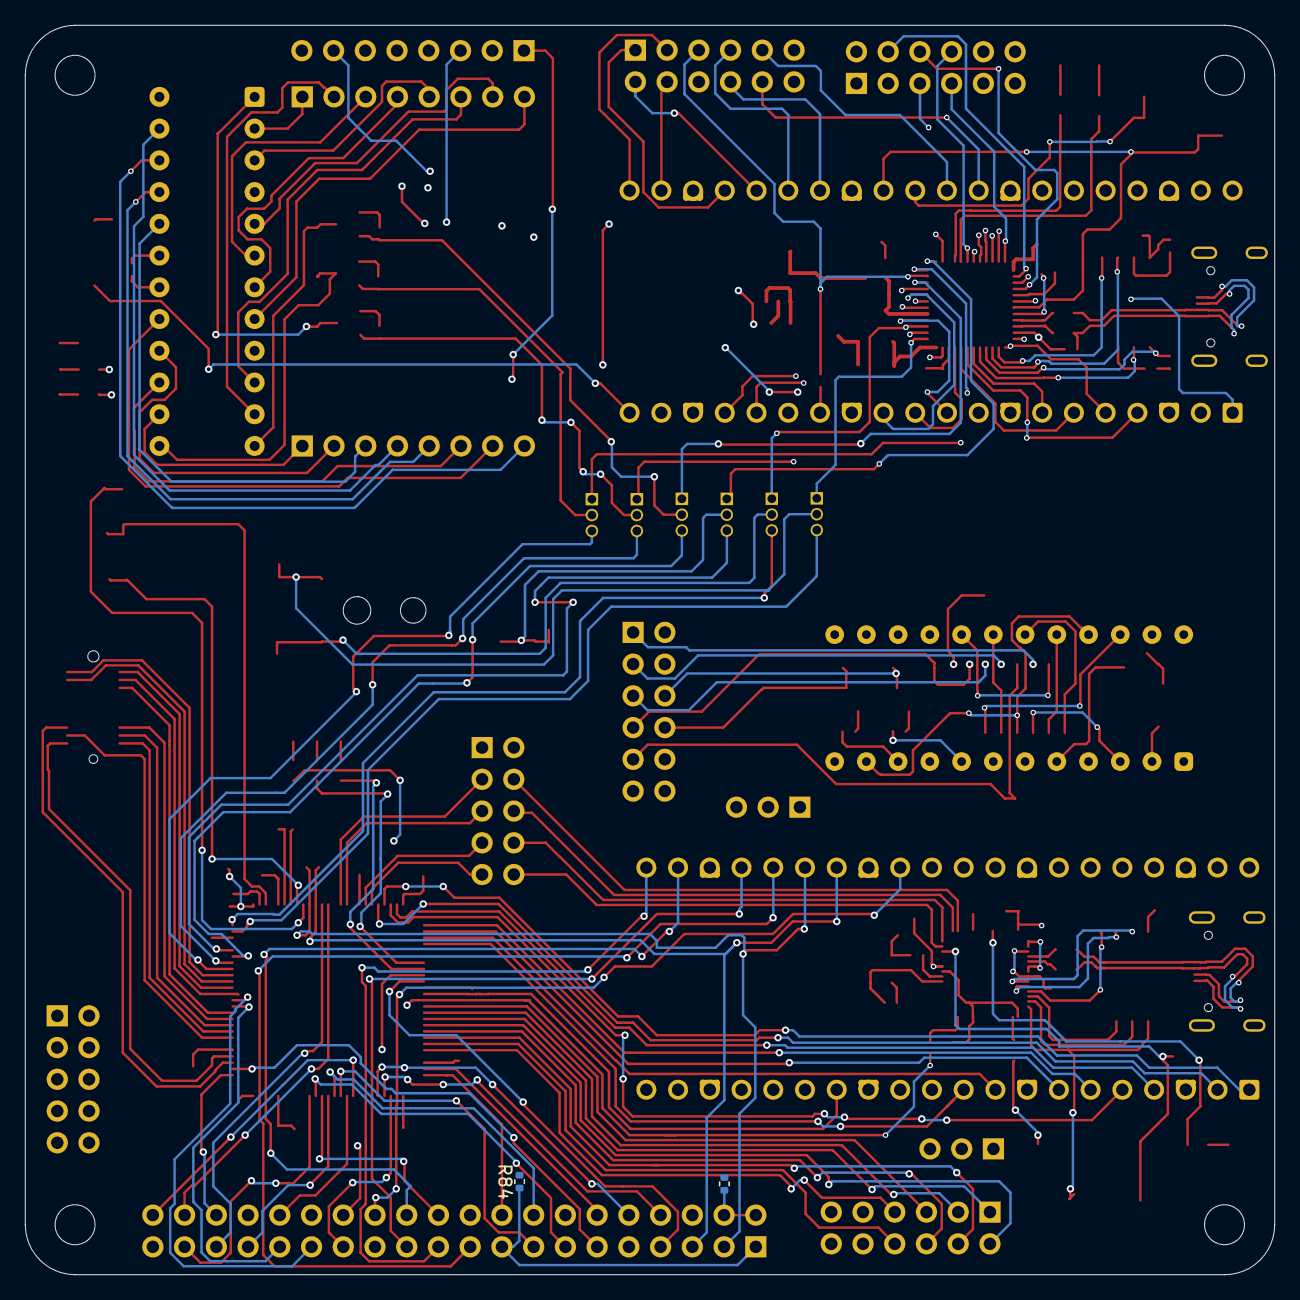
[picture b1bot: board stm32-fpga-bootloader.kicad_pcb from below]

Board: 4 copper layers, 100.0 x 100.0 mm, 183 parts (2 on the bottom side), 241 nets.

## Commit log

2025-05-23 Update the design files
2025-05-24 Update the schematic
2025-05-28 update the source code
2025-06-02 Update the source code
2025-06-03 Update the source files
2025-06-06 Update the footprints
2025-06-09 Update the BOM and the routing
2025-06-12 Rework on pins assignements
2025-06-17 Updqte schematic
2025-06-22 Improve the routing
